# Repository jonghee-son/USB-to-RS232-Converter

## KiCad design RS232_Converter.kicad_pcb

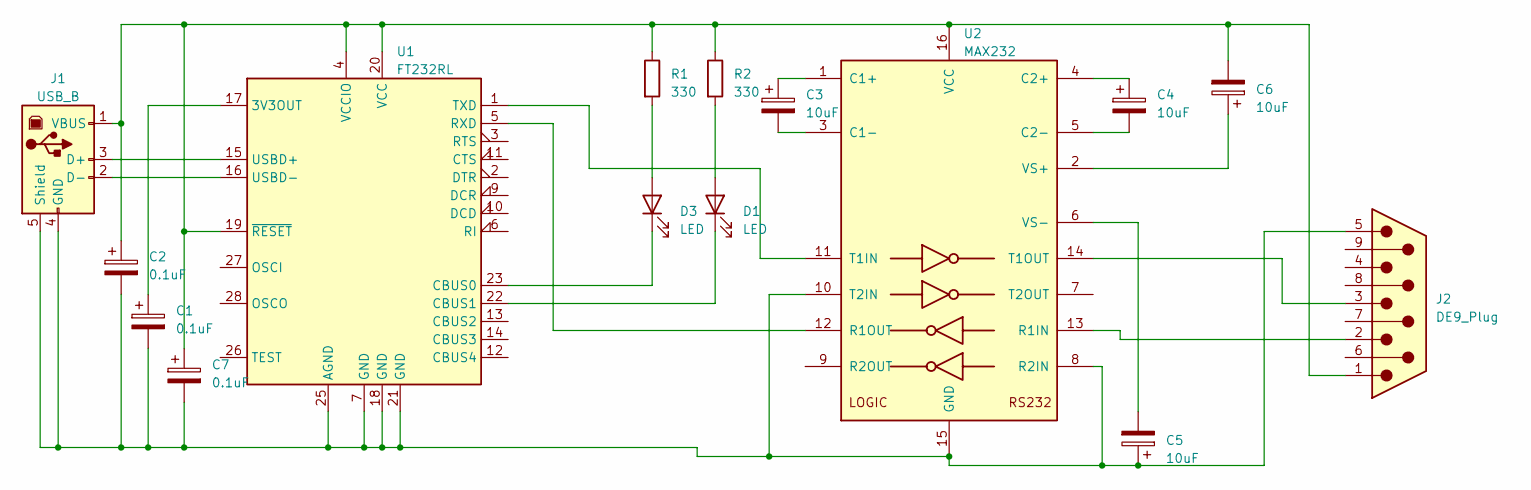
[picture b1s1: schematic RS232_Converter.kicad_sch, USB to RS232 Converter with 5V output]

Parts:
C1, C2, C7: 0.1uF; C_Disc_D5.0mm_W2.5mm_P5.00mm
C3, C4, C5, C6: 10uF; CP_Radial_Tantal_D4.5mm_P2.50mm
D1, D3: LED; LED_D5.0mm
J1: USB_B; USB_B_Lumberg_2411_02_Horizontal
J2: DE9_Plug; DSUB-9_Female_Horizontal_P2.77x2.54mm_EdgePinOffset9.40mm
R1, R2: 330; R_Axial_DIN0207_L6.3mm_D2.5mm_P10.16mm_Horizontal
U1: FT232RL; SSOP-28_5.3x10.2mm_P0.65mm
U2: MAX232; DIP-16_W7.62mm

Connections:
unnamed: D1.2 (A), R2.2
unnamed: D1.1 (K), U1.22 (CBUS1)
unnamed: D3.2 (A), R1.2
unnamed: D3.1 (K), U1.23 (CBUS0)
unnamed: J1.3 (D+), U1.15 (USBD+)
unnamed: J1.2 (D-), U1.16 (USBD-)
unnamed: C1.2, C2.2, C5.1, C7.2, J1.4 (GND), J1.5 (Shield), J2.5, U1.7 (GND), U1.18 (GND), U1.21 (GND), U1.25 (AGND), U2.8 (R2IN), U2.10 (T2IN), U2.15 (GND)
unnamed: C2.1, C6.2, C7.1, J1.1 (VBUS), J2.1, R1.1, R2.1, U1.4 (VCCIO), U1.19 (~RESET), U1.20 (VCC), U2.16 (VCC)
unnamed: C1.1, U1.17 (3V3OUT)
unnamed: U1.5 (RXD), U2.12 (R1OUT)
unnamed: U1.1 (TXD), U2.11 (T1IN)
unnamed: C3.1, U2.1 (C1+)
unnamed: C3.2, U2.3 (C1-)
unnamed: C4.1, U2.4 (C2+)
unnamed: C4.2, U2.5 (C2-)
unnamed: J2.2, U2.13 (R1IN)
unnamed: J2.3, U2.14 (T1OUT)
unnamed: C6.1, U2.2 (VS+)
unnamed: C5.2, U2.6 (VS-)

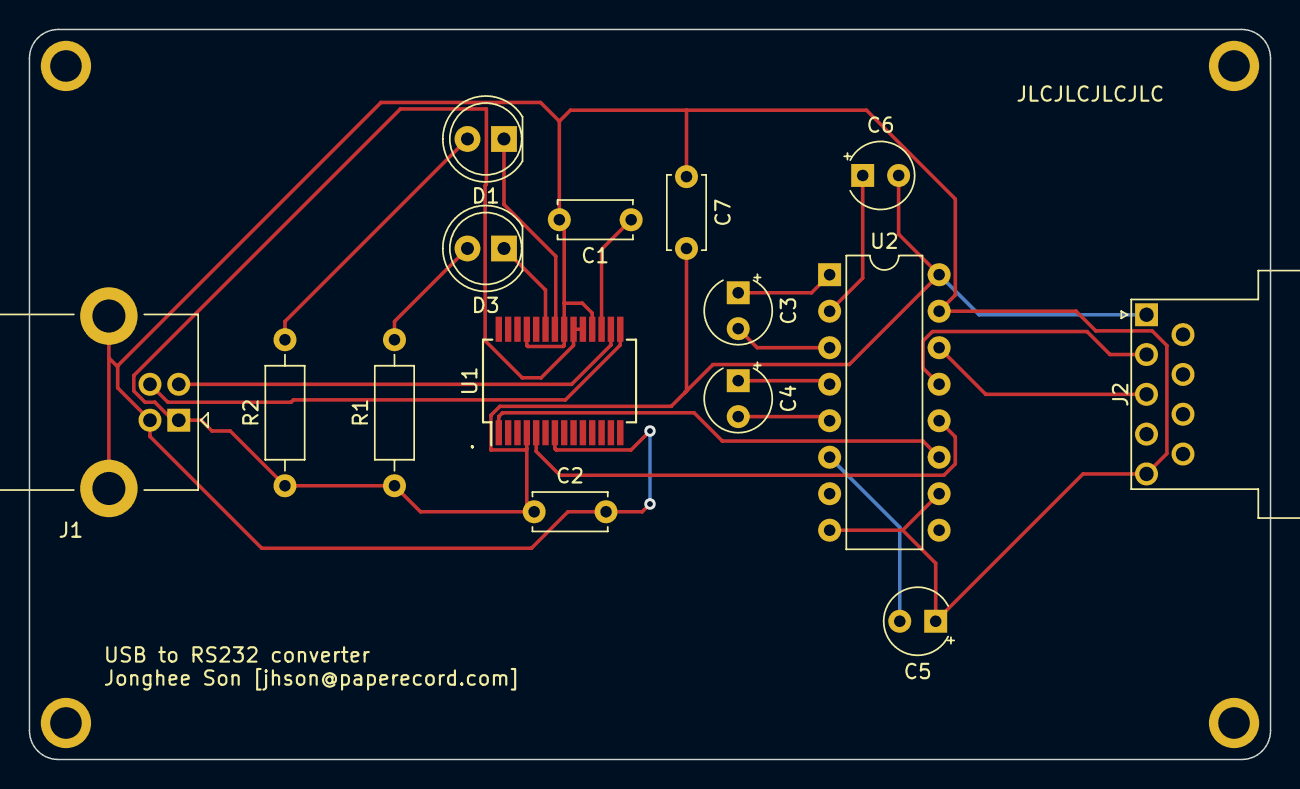
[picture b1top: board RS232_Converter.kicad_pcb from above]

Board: 2 copper layers, 86.4 x 50.8 mm, 15 parts (0 on the bottom side), 19 nets.

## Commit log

2023-04-09 Create LICENSE
2023-11-07 Added .gitignore
